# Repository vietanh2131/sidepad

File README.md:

# sidepad
a vietanh's miniproject, with support from [highway to hardware by hack club](https://highway.hackclub.com/)

## what i used
1x Seeed XIAO RP2040
6x MX-Style switches
1x EC11 Rotary encoder
1x sugar
1x spice
1x everything nice

i used KiCAD for the pcb designs, Fusion for the case and QMK for the firmware

## pictures

insert real sidepad image here

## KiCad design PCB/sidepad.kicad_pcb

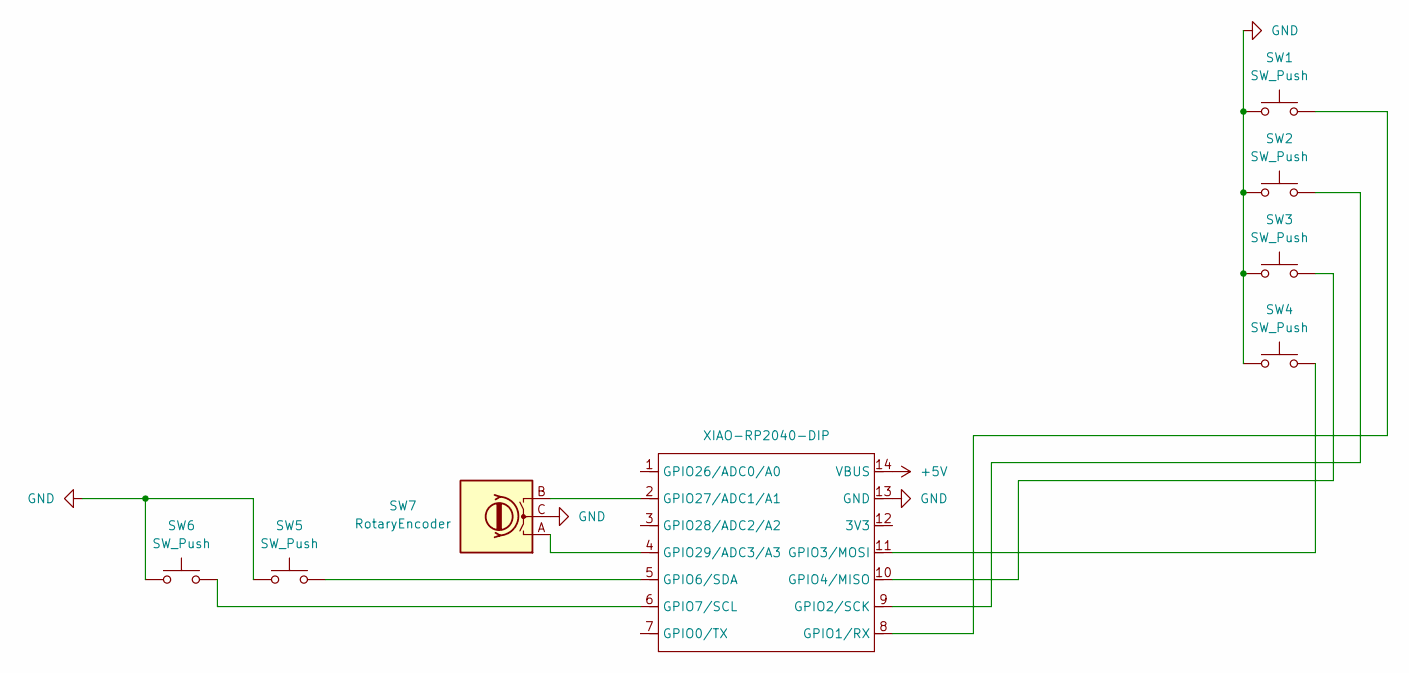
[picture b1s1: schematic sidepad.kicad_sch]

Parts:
SW1, SW2, SW3, SW4, SW5, SW6: SW_Push; SW_Cherry_MX_1.00u_PCB
SW7: RotaryEncoder; RotaryEncoder_Alps_EC11E-Switch_Vertical_H20mm
U1: XIAO-RP2040-DIP

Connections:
+5V: U1.14 (VBUS)
GND: SW1.1, SW2.1, SW3.1, SW4.1, SW5.1, SW6.1, SW7.C, U1.13 (GND)
unnamed: SW1.2, U1.8 (GPIO1/RX)
unnamed: SW2.2, U1.9 (GPIO2/SCK)
unnamed: SW4.2, U1.11 (GPIO3/MOSI)
unnamed: SW3.2, U1.10 (GPIO4/MISO)
unnamed: SW5.2, U1.5 (GPIO6/SDA)
unnamed: SW6.2, U1.6 (GPIO7/SCL)
unnamed: SW7.B, U1.2 (GPIO27/ADC1/A1)
unnamed: SW7.A, U1.4 (GPIO29/ADC3/A3)

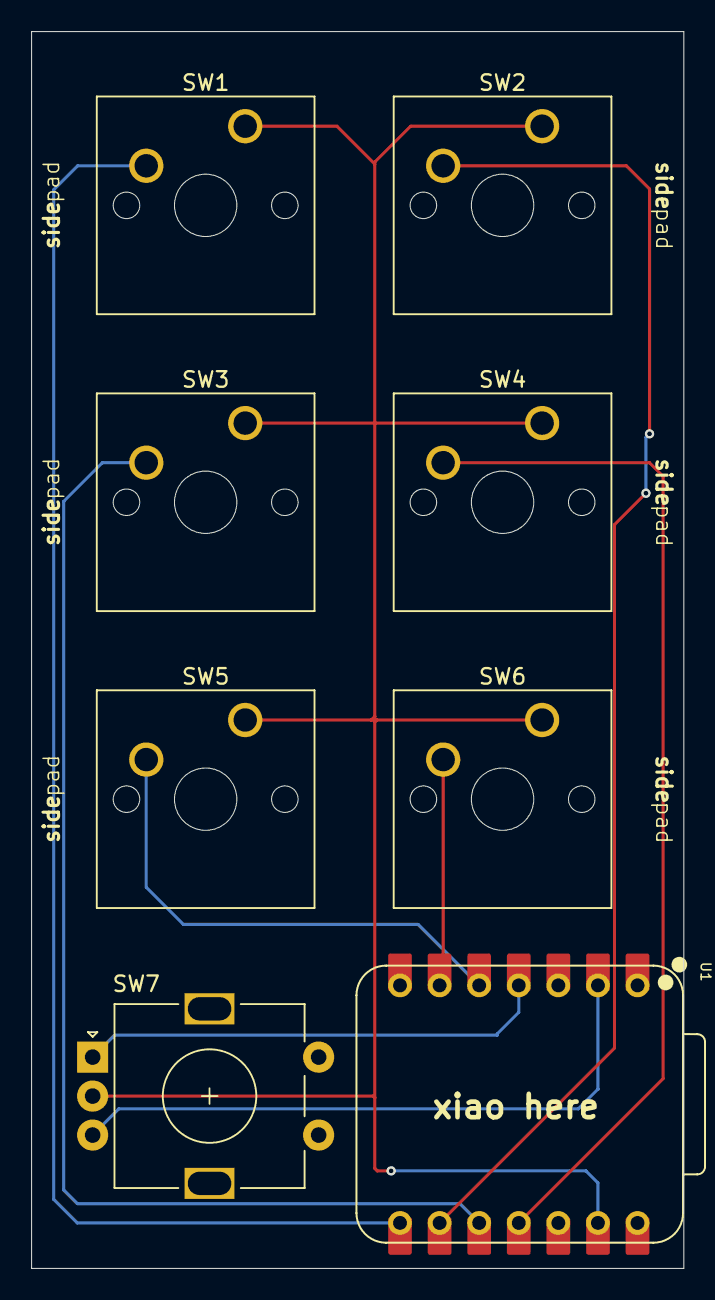
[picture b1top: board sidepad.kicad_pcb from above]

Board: 2 copper layers, 41.9 x 79.4 mm, 8 parts (0 on the bottom side), 9 nets.

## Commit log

2025-07-16 uploading the firmware
2025-07-16 Create tmp
2025-07-16 Rename config.h to config.h
2025-07-16 Rename gerber.zip to gerbers.zip
